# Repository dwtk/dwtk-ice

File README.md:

# dwtk-ice

An USB-connected In-Circuit Emulator for [dwtk](https://github.com/rafaelmartins/dwtk).

## Hardware

### Schematics

#### Bill of materials

ID | Description | Reichelt Item no.
-- | ----------- | -----------------
U1 | ATtiny4313 | ATTINY 4313 PU
Q1 | BC548B | BC 548B
Y1 | Crystal 20,000MHz | 20,0000-HC49U-S
D1, D2 | Zener diode 3,6V | ZF 3,6
LED1 | LED Red 5mm | LED 5MM RT
LED2 | LED Green 5mm | LED 5MM GN
C1 | Electrolytic capacitor 10uF/35V | RAD 10/35
C2 | Multi-layer ceramic capacitor 100nF | X7R-5 100N
C3, C4 | Ceramic capacitor 22pF | KERKO 22P
R1, R2 | Carbon film resistor 1/4 W, 5%, 68 Ohm| 1/4W 68
R3 | Carbon film resistor 1/4 W, 5%, 2,2K Ohm | 1/4W 2,2K
R4, R5 | Carbon film resistor 1/4 W, 5%, 1,5K Ohm | 1/4W 1,5K
R6 | Carbon film resistor 1/4 W, 5%, 22K Ohm | 1/4W 22K
R7 | Carbon film resistor 1/4 W, 5%, 470 Ohm | 1/4W 470
USB1 | USB panel socket, type A | RND 205-00660
H1 + H2 | Header pins 1x40 | SL 1X40G 2,54
&nbsp; | IC socket, 20-pin | GS 20
&nbsp; | Prototype PCB 3cm x 7cm | &nbsp;

### Prototype

### DISCLAIMER

THIS PROJECT IS PROVIDED AS IS. USE IT AT YOUR OWN RISK. THIS DEVICE IS USB CONNECTED AND MAY DAMAGE YOUR COMPUTER.

The USB connections in the schematics are there just for reference, please check the actual pinout of your connector before assembling and/or using.

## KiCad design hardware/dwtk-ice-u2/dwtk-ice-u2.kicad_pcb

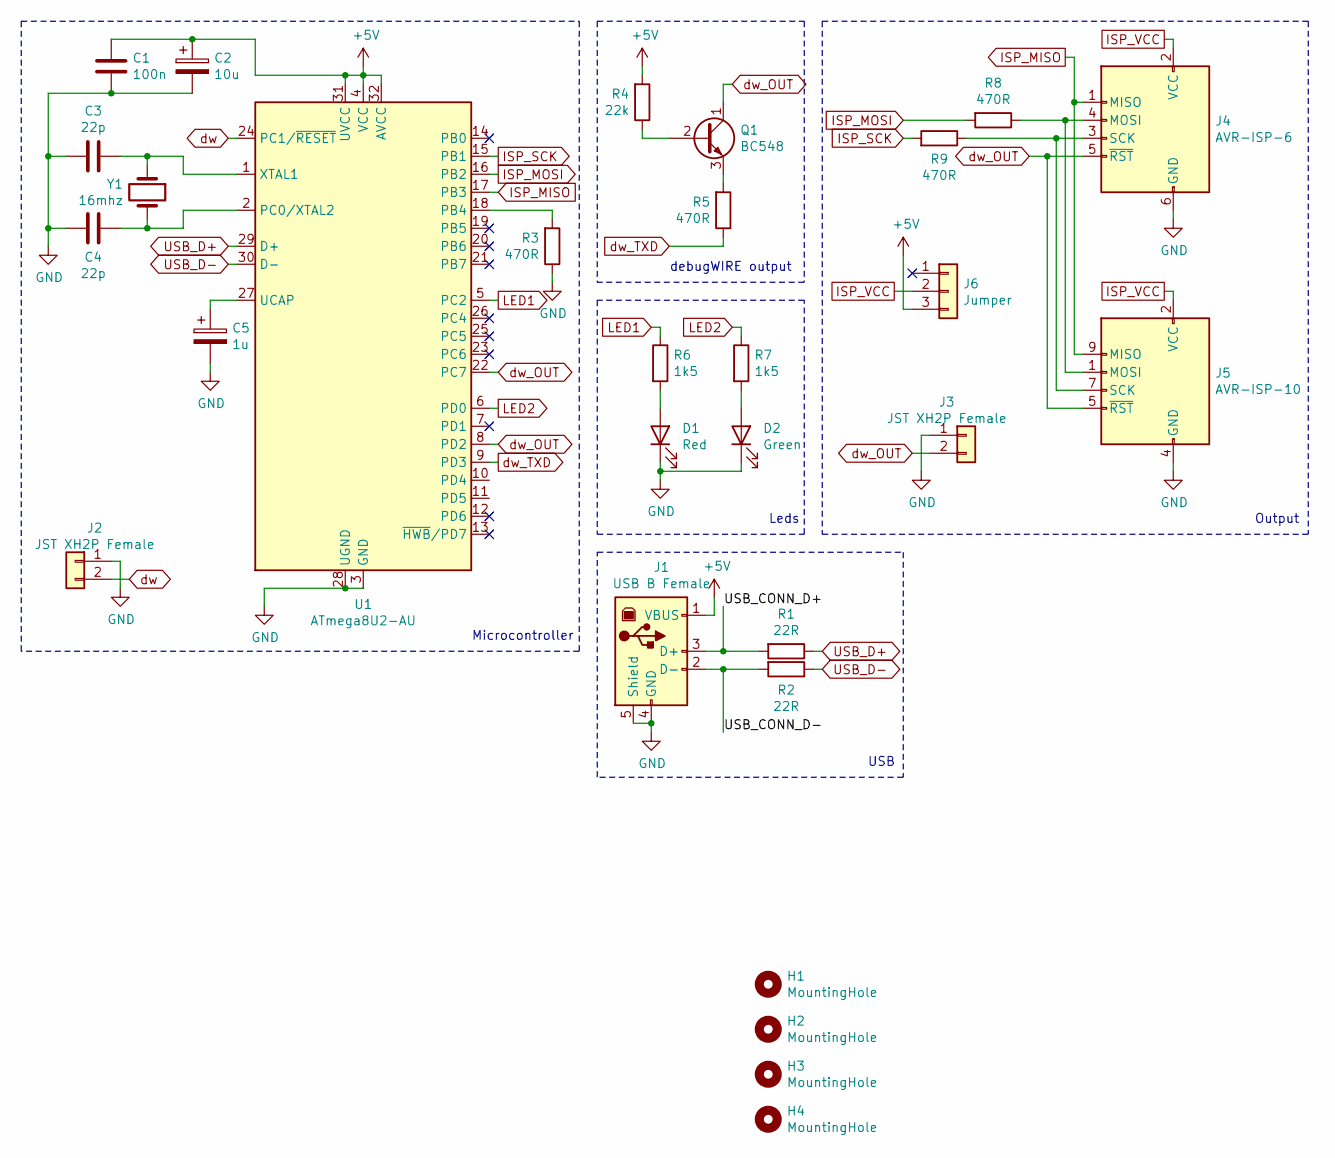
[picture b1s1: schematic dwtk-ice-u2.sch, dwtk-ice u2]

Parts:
C1: 100n; C_Disc_D4.3mm_W1.9mm_P5.00mm; Mouser Ref. 594-K104K15X7RF53K2
C2: 10u; CP_Radial_D5.0mm_P2.50mm; Mouser Ref. 667-ECA-1VM100I
C3, C4: 22p; C_Disc_D3.0mm_W1.6mm_P2.50mm; Mouser Ref. 594-K220J15C0GF53L2
C5: 1u; CP_Radial_D5.0mm_P2.50mm; Mouser Ref. 667-ECA-2VM010B
D1: Red; LED_D3.0mm; Mouser Ref. 604-WP710A10SEC/J3
D2: Green; LED_D3.0mm; Mouser Ref. 604-WP710A10ZGC/G
H1, H2, H3, H4: MountingHole; MountingHole_2.2mm_M2_Pad_Via
J1: USB B Female; USB_B_Lumberg_2411_02_Horizontal; Mouser Ref. 710-61400416121
J2, J3: JST XH2P Female; JST_XH_B2B-XH-A_1x02_P2.50mm_Vertical; Mouser Ref. N/A
J4: AVR-ISP-6; IDC-Header_2x03_P2.54mm_Vertical; Mouser Ref. 710-61200621621
J5: AVR-ISP-10; IDC-Header_2x05_P2.54mm_Vertical; Mouser Ref. 710-61201021621
J6: Jumper; PinHeader_1x03_P2.54mm_Vertical; Mouser Ref. 68797-236HLF
Q1: BC548; TO-92_Inline; Mouser Ref. 821-BC548B-A1
R1, R2: 22R; R_Axial_DIN0207_L6.3mm_D2.5mm_P10.16mm_Horizontal; Mouser Ref. 603-MFR-25FTF52-22R
R3, R5, R8, R9: 470R; R_Axial_DIN0207_L6.3mm_D2.5mm_P10.16mm_Horizontal; Mouser Ref. 603-MFR-25FTF52-470R
R4: 22k; R_Axial_DIN0207_L6.3mm_D2.5mm_P10.16mm_Horizontal; Mouser Ref. 603-MFR-25FTF52-22K
R6, R7: 1k5; R_Axial_DIN0207_L6.3mm_D2.5mm_P10.16mm_Horizontal; Mouser Ref. 603-MFR-25FTF52-1K5
U1: ATmega8U2-AU; TQFP-32_7x7mm_P0.8mm_LongPads; Mouser Ref. 556-ATMEGA8U2-AU
Y1: 16mhz; Crystal_HC49-U_Vertical; Mouser Ref. 815-ABL-16-B4Y

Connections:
+5V: C1.1, C2.1, J1.1 (VBUS), J6.3, R4.2, U1.4 (VCC), U1.31 (UVCC), U1.32 (AVCC)
/USB_CONN_D+: J1.3 (D+), R1.2
/USB_CONN_D-: J1.2 (D-), R2.2
GND: C1.2, C2.2, C3.2, C4.2, C5.2, D1.1 (K), D2.1 (K), J1.4 (GND), J1.5 (Shield), J2.1, J3.1, J4.6 (GND), J5.4 (GND), J5.6 (GND), J5.8 (GND), J5.10 (GND), R3.1, U1.3 (GND), U1.28 (UGND)
ISP_MISO: J4.1 (MISO), J5.9 (MISO), U1.17 (PB3)
ISP_MOSI: R8.2, U1.16 (PB2)
ISP_SCK: R9.2, U1.15 (PB1)
ISP_VCC: J4.2 (VCC), J5.2 (VCC), J6.2
LED1: R6.1, U1.5 (PC2)
LED2: R7.1, U1.6 (PD0)
unnamed: C3.1, U1.1 (XTAL1), Y1.1
unnamed: C4.1, U1.2 (PC0/XTAL2), Y1.2
unnamed: C5.1, U1.27 (UCAP)
unnamed: D1.2 (A), R6.2
unnamed: D2.2 (A), R7.2
unnamed: J4.3 (SCK), J5.7 (SCK), R9.1
unnamed: J4.4 (MOSI), J5.1 (MOSI), R8.1
unnamed: Q1.2 (B), R4.1
unnamed: Q1.3 (E), R5.2
unnamed: R3.2, U1.18 (PB4)
USB_D+: R1.1, U1.29 (D+)
USB_D-: R2.1, U1.30 (D-)
dw: J2.2, U1.24 (PC1/~RESET)
dw_OUT: J3.2, J4.5 (~RST), J5.5 (~RST), Q1.1 (C), U1.8 (PD2), U1.22 (PC7)
dw_TXD: R5.1, U1.9 (PD3)

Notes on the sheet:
Leds
Microcontroller
USB
Output
debugWIRE output

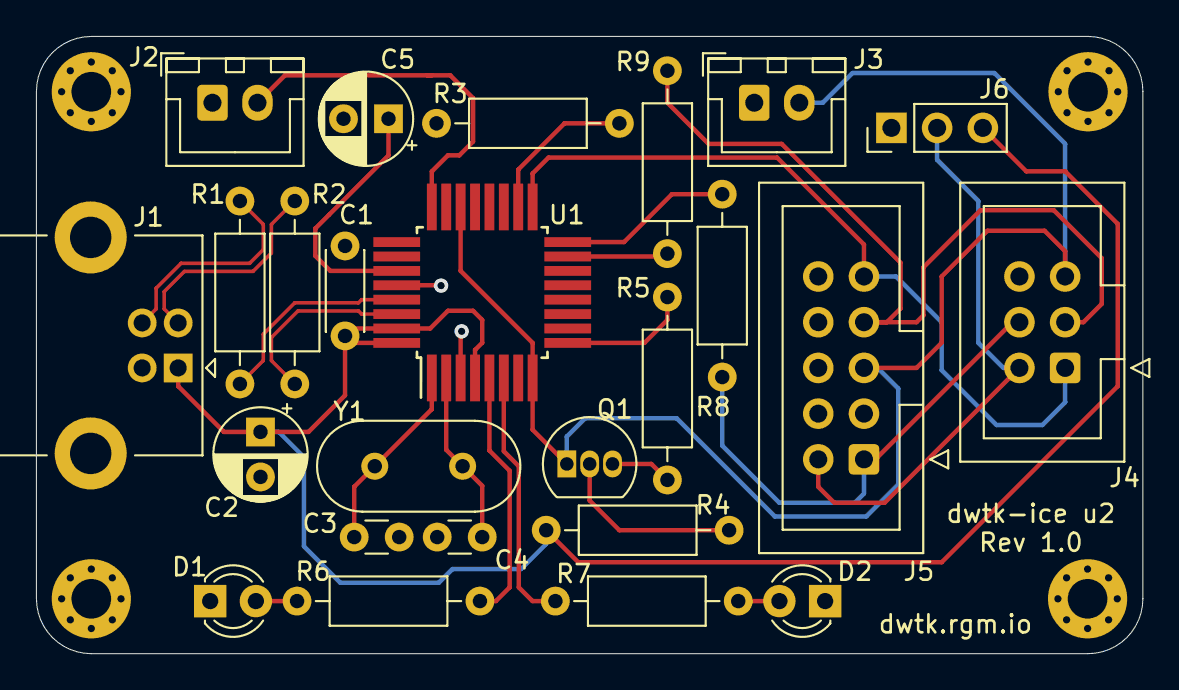
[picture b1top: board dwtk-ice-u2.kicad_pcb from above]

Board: 2 copper layers, 61.5 x 34.3 mm, 29 parts (0 on the bottom side), 25 nets.

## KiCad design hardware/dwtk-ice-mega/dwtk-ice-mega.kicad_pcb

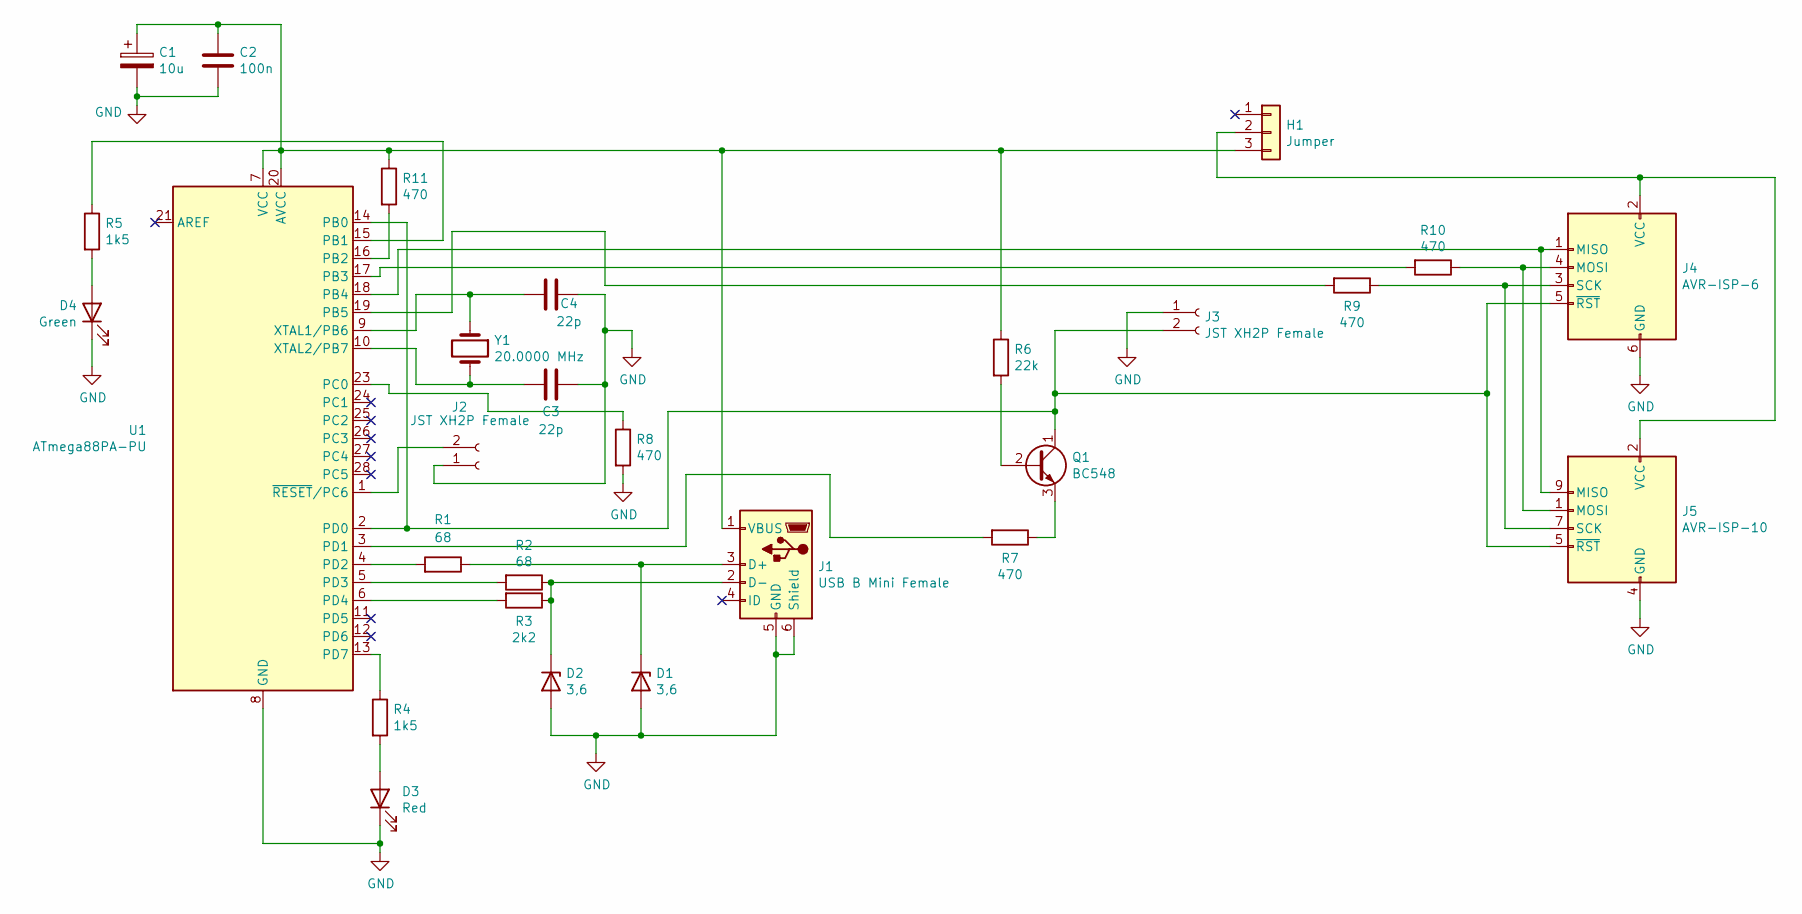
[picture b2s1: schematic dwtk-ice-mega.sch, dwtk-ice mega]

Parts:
C1: 10u; CP_Radial_D4.0mm_P2.00mm
C2: 100n; C_Disc_D3.0mm_W1.6mm_P2.50mm
C3, C4: 22p; C_Disc_D3.0mm_W1.6mm_P2.50mm
D1, D2: 3,6; D_DO-35_SOD27_P7.62mm_Horizontal
D3: Red; LED_D3.0mm
D4: Green; LED_D3.0mm
H1: Jumper; PinHeader_1x03_P2.54mm_Vertical
J1: USB B Mini Female; RND_205-00862
J2, J3: JST XH2P Female; JST_XH_B2B-XH-A_1x02_P2.50mm_Vertical
J4: AVR-ISP-6; IDC-Header_2x03_P2.54mm_Vertical
J5: AVR-ISP-10; IDC-Header_2x05_P2.54mm_Vertical
Q1: BC548; TO-92_Inline
R1, R2: 68; R_Axial_DIN0207_L6.3mm_D2.5mm_P10.16mm_Horizontal
R3: 2k2; R_Axial_DIN0207_L6.3mm_D2.5mm_P10.16mm_Horizontal
R4, R5: 1k5; R_Axial_DIN0207_L6.3mm_D2.5mm_P10.16mm_Horizontal
R6: 22k; R_Axial_DIN0207_L6.3mm_D2.5mm_P10.16mm_Horizontal
R7, R8, R9, R10, R11: 470; R_Axial_DIN0207_L6.3mm_D2.5mm_P10.16mm_Horizontal
U1: ATmega88PA-PU; DIP-28_W7.62mm
Y1: 20.0000 MHz; Crystal_HC49-U_Vertical

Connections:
GND: C1.2, C2.2, C3.1, C4.1, D1.2 (A), D2.2 (A), D3.1 (K), D4.1 (K), J1.5 (GND), J1.6 (Shield), J2.1, J3.1, J4.6 (GND), J5.4 (GND), J5.6 (GND), J5.8 (GND), J5.10 (GND), R8.2, U1.8 (GND), U1.22 (GND)
unnamed: C1.1, C2.1, H1.3, J1.1 (VBUS), R6.1, R11.1, U1.7 (VCC), U1.20 (AVCC)
unnamed: C3.2, U1.10 (XTAL2/PB7), Y1.2
unnamed: C4.2, U1.9 (XTAL1/PB6), Y1.1
unnamed: D1.1 (K), J1.3 (D+), R1.1
unnamed: D2.1 (K), J1.2 (D-), R2.1, R3.1
unnamed: D3.2 (A), R4.2
unnamed: D4.2 (A), R5.2
unnamed: H1.2, J4.2 (VCC), J5.2 (VCC)
unnamed: J2.2, U1.1 (~RESET~/PC6)
unnamed: J3.2, J4.5 (~RST), J5.5 (~RST), Q1.1 (C), U1.2 (PD0), U1.14 (PB0)
unnamed: J4.1 (MISO), J5.9 (MISO), U1.18 (PB4)
unnamed: J4.3 (SCK), J5.7 (SCK), R9.1
unnamed: J4.4 (MOSI), J5.1 (MOSI), R10.1
unnamed: Q1.2 (B), R6.2
unnamed: Q1.3 (E), R7.1
unnamed: R1.2, U1.4 (PD2)
unnamed: R2.2, U1.5 (PD3)
unnamed: R3.2, U1.6 (PD4)
unnamed: R4.1, U1.13 (PD7)
unnamed: R5.1, U1.15 (PB1)
unnamed: R7.2, U1.3 (PD1)
unnamed: R8.1, U1.23 (PC0)
unnamed: R9.2, U1.19 (PB5)
unnamed: R10.2, U1.17 (PB3)
unnamed: R11.2, U1.16 (PB2)

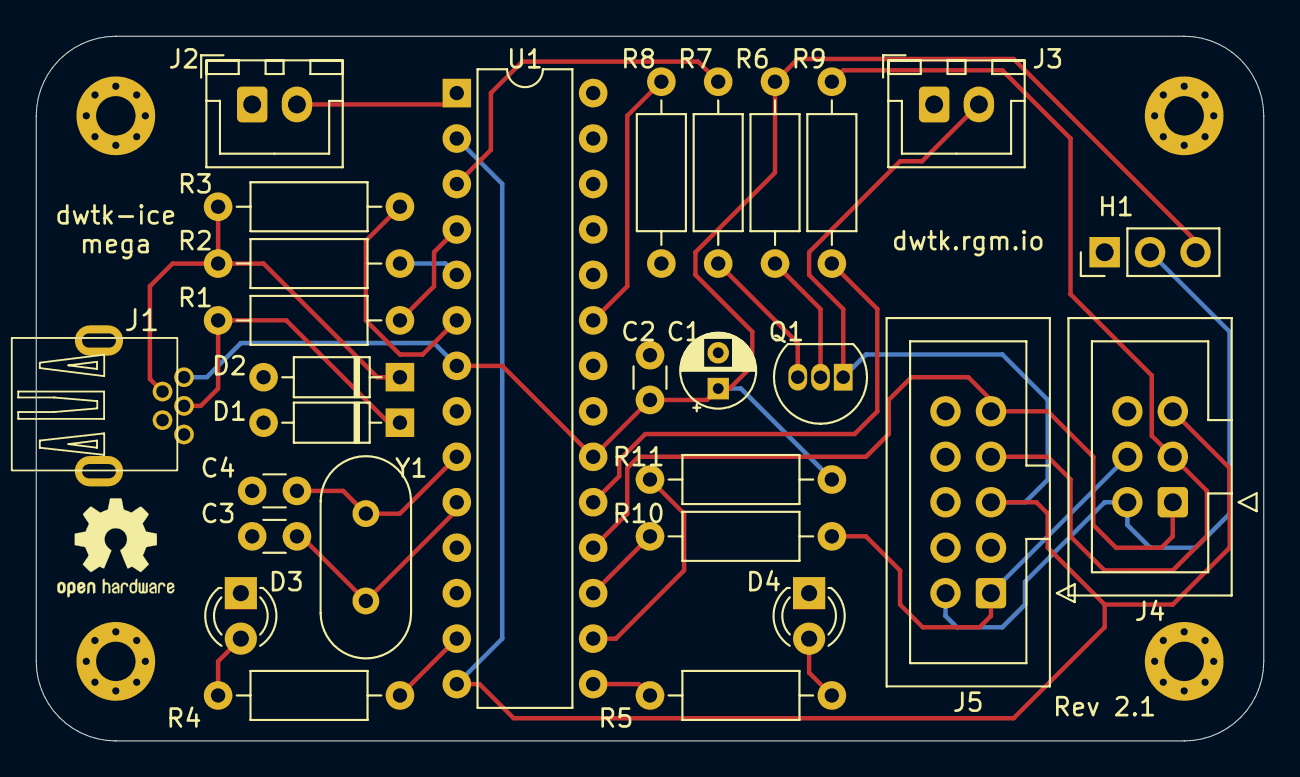
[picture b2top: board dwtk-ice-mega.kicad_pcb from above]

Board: 2 copper layers, 68.6 x 39.4 mm, 28 parts (0 on the bottom side), 26 nets.

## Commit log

2019-12-27 Initial codebase
2019-12-30 Add leds
2019-12-30 Support writing flash pages
2019-12-30 Reorder static variables
2019-12-30 Use our new USB VID/PID. Thanks to OpenMoko
2019-12-31 Support erasing flash pages
2020-01-01 minor optimization
2020-01-02 removed hardcoded UBRRs
2020-01-02 Use a static buffer when reading/writing to target device
2020-01-02 Populate README with some hardware information
2020-01-02 Add leds Reichelt item numbers
2020-01-04 added disclaimer
2020-01-05 send break after set baudrate, to validate
2020-01-05 enable U2X to increase baudrate resolution
    this also round up UBRR if needed, with some tricks to avoid doing float
    division
2020-01-05 detect baudrate from lower to faster frequency
2020-01-05 reset watchdog before set baudrate. increase watchdog timer to 2s
2020-01-07 refuse read requests to CMD_WRITE_FLASH_PAGE
2020-01-17 support reading fuses
2020-01-24 major rewrite
    - detect baudrate only during startup, measuring break bit width
    - removed some request types
    - reset device after returning an error
    schematics are outdated
2020-01-28 size optimization
2020-01-29 re-added commands to detect baudrate and retrieve signature
    detecting baudrate during startup is hard to handle, lets allow clients
    to request baudrate detection themselves.
    also re-added command to get baudrate, because the detection is done
    after the usb request.
    warning: this implementation requires waiting for at least 4ms after
    requesting baudrate detection, before sending any other requests,
2020-01-29 define some macros to calculate instruction opcodes
2020-02-03 allow changes to break time during compilation
2020-02-05 reset usart before detecting pulse width
2020-02-05 add some context to error reporting
2020-02-11 reduce default break time, in us instead of ms
2020-02-11 update schematics and prototype pictures
2020-02-11 minor readme fix
2020-02-12 minor fix
2020-02-12 Makefile: do not mess with lockbits
2020-02-12 update prototype pictures
2020-02-21 added minimal SPI support to allow setting fuses
    WARNING: this code does not work with current dwtk git master, and does
    not matches the schematics from this repository.
2020-02-21 allow to disable spi by releasing reset
2020-02-22 regression: send break before reset
2020-02-23 minor change
2020-02-23 added SPI reset command
2020-02-29 fixed wrong variable size
2020-02-29 added capabilities support, to report if dw/spi is supported
2020-03-03 use new makefile
2020-03-03 build: ci: trying to generate builds automatically
2020-03-03 warn users to not edit makefile
2020-03-05 build: ci: yatr knows how to build avr stuff now
2020-03-08 fix include
2020-03-08 use new dwtk-makefile
2020-03-08 revert changes to dwtk-config.mk
2020-03-12 read usb serial number from eeprom if available.
    currently there's no easy way to write the data to eeprom, but if
    there's an 8 bytes string at the start of eeprom, it will be used as the
    serial number.
2020-04-01 store serial number on eeprom as a 32 bit unsigned integer
2020-04-01 build: disable debug build
2020-04-02 Revert "build: disable debug build"
    This reverts commit a67d82a39db0e28c5c14fba6a12735ff589ef081.
2020-04-02 calculate break time from pulse width.
    big delays are needed only for flash write/erase. this change will
    speedup all the other operations.
    right now, the debug builds are using exactly the 4kB of flash we have
    in the attiny4313 :/
2020-04-03 fixed serial number
2020-04-03 added makefile rule to generate and write serial number
2020-04-10 updated Makefile from dwtk-makefile
2020-06-23 remove usbRxLen usage
2020-06-28 fixed request length. error is not part of request
2020-07-04 initial port to atmega88a
    this is not tested. need to build a prototype and validate.
2020-07-08 fix atmega88pa replacement for TIFR
    it provides a separated TIFR for timer 1
2020-07-09 improve spm calls during flash
2020-07-09 support MCUs with RWW flash area
2020-07-09 remove broken urls
2020-07-09 do not implement fuses reading for attiny4313 debug builds
    this saves us some flash space, to allow us having debug builds for
    attiny4313. the software implementation in dwtk is fast enough for most
    use cases anyway.
2020-07-09 build: generate firmware builds for multiple mcus
2020-07-16 atmega88pa: increase SPI prescaler, to reduce frequency.
    the slower SPI frequency works fine for all the range of target MCU
    frequencies, while the old one would fail for slower target MCUs.
2020-10-11 hardware: initial import of kicad schematics and pcbs
2020-10-11 build: github-actions: fix syntax
2020-10-12 build: github-actions: generate interactive boms
2020-10-14 hardware: update dwtk-ice-mega pcb values
2020-10-14 hardware: added mouser references
2021-01-05 usbconfig: fixed vendor name
2022-01-07 support atmega{8,16,32}u2 native USB 2.0 devices
2022-01-07 actions: do not upload bom if not master or tag build
